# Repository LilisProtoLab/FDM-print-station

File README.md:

# FDM print station
For a number of FDM 3D printing materials it is of importance to store and use them under low relative humidity conditions. 
For this purpose a station was designed, containing an adapter drawer with two storage compartments, and three 3D printer compartments. For each compartment relative humidity (and temperature) can be monitored and controlled by flushing with dried compressed air. 

## Main features
This FDM print station contains:
+ A humidity control system
	+ Building-supplied compressed air is fed through a membrane dryer (DM08G-19KA-N) to reduce the moisture level
   	+ Each compartment contains a sensor unit which monitors temperature, humidity and door open status
   		+ Door sensors make sure flushing is only active while the compartments are closed
   	+ Five electronic valves direct the flow of pressured air to each compartment
   	+ Dried air is distributed to five compartments: two drawer compartments, and three printer compartments
   	+ Home Assistant integration controls the humidity setpoints for the drawer compartments (typically 12%) and the printer enclosures (typically 20%)
+ One filament storage drawer with two compartments
	+ A pre-existing drawer is supplemented with a transparant PMMA enclosure for convenient selection of materials with the lids closed	
	+ A screen mounted to the drawer displays the current humidity, temperature and door sensors + flushing status of all compartments
+ Three printer enclosures
	+ vertical sliding doors for minimal obstruction from 5mm PMMA sheets, with 3D printed handles and latches.
	+  The exhaust ventilation is connected to the building exhaust system and controlled via manual, 3D printed gate valves.
	+ The enclosure is made from aluminium extrusions with 3mm PMMA sheet walls

```
.
|--- Build 
|--- Docs
|--- Results
|--- Software
| LICENSE
| README.md

```

The purpose of each subfolder is explained below:
+ Build: Contains all the (binary) design files that are needed for the hardware. Use subfolder for more complex assemblies.
+ Docs: Contains the documentation of the project: background information, sources, warnings, and build instructions. 
+ Results: For measurement or functional devices, it is good to report some results as a benchmark for others who try to replicate the project.
+ Software: For hardware projects that have an operating software or firmware, it is a good versioning practice to separate the software code from build instructions.

## Build instructions
_Guide the reader with the order of browsing your project repository for an optimum building experience_
 
When you want to start a new repository, it is better that you copy this repository to your project repository and start by changing all the description.
All instructions and (sub)headers are suggestions. You can change the style, order, or composition as you see necessary. 

It would be kind if you put a shortcut to your Bill of Materials file.
This template can be copied free of charge. 

## Outcomes

## Team
+ Project initiator: Pieter Kooijman @pkooijman
+ Contributors:
	+ Josh Hauser @catoprovector
 	+ Nico van Hijningen

## Get involved
_Especially for open source projects, it is benefitial to motivate the potential users of the project to contribute back or share their feedback. Make it easy for them._

Comments and suggestions on this folder structure are always welcome. Please create an issue to share your feedback or question, or if you prefer send a pull request. 

Better structured projects can explain a number of options for contributors such as: 
+ (where to start)
+ (issue template)
+ (direct contact)
+ (pull requests)

## License
_After the README, A LICENSE is the most important file in the project documentation. Without a license, there is too much uncertainty to try building anything on top of the original project._

This project is released under CC0 1.0 Universal. 
You can modify an reuse as you like.
The project team appreciates your suggestions or examples for enhancing the repository, but your consistent documentation of your project is the best gift to the world. Hopefully, this template could make that a bit easier for you. 

### (How to cite:)
_Additionally, you can specify how other can cite your project._

## (Funding)
_Be kind to your funders and mention their support visibly and consistently. They also need to show their resources are wisely spent._

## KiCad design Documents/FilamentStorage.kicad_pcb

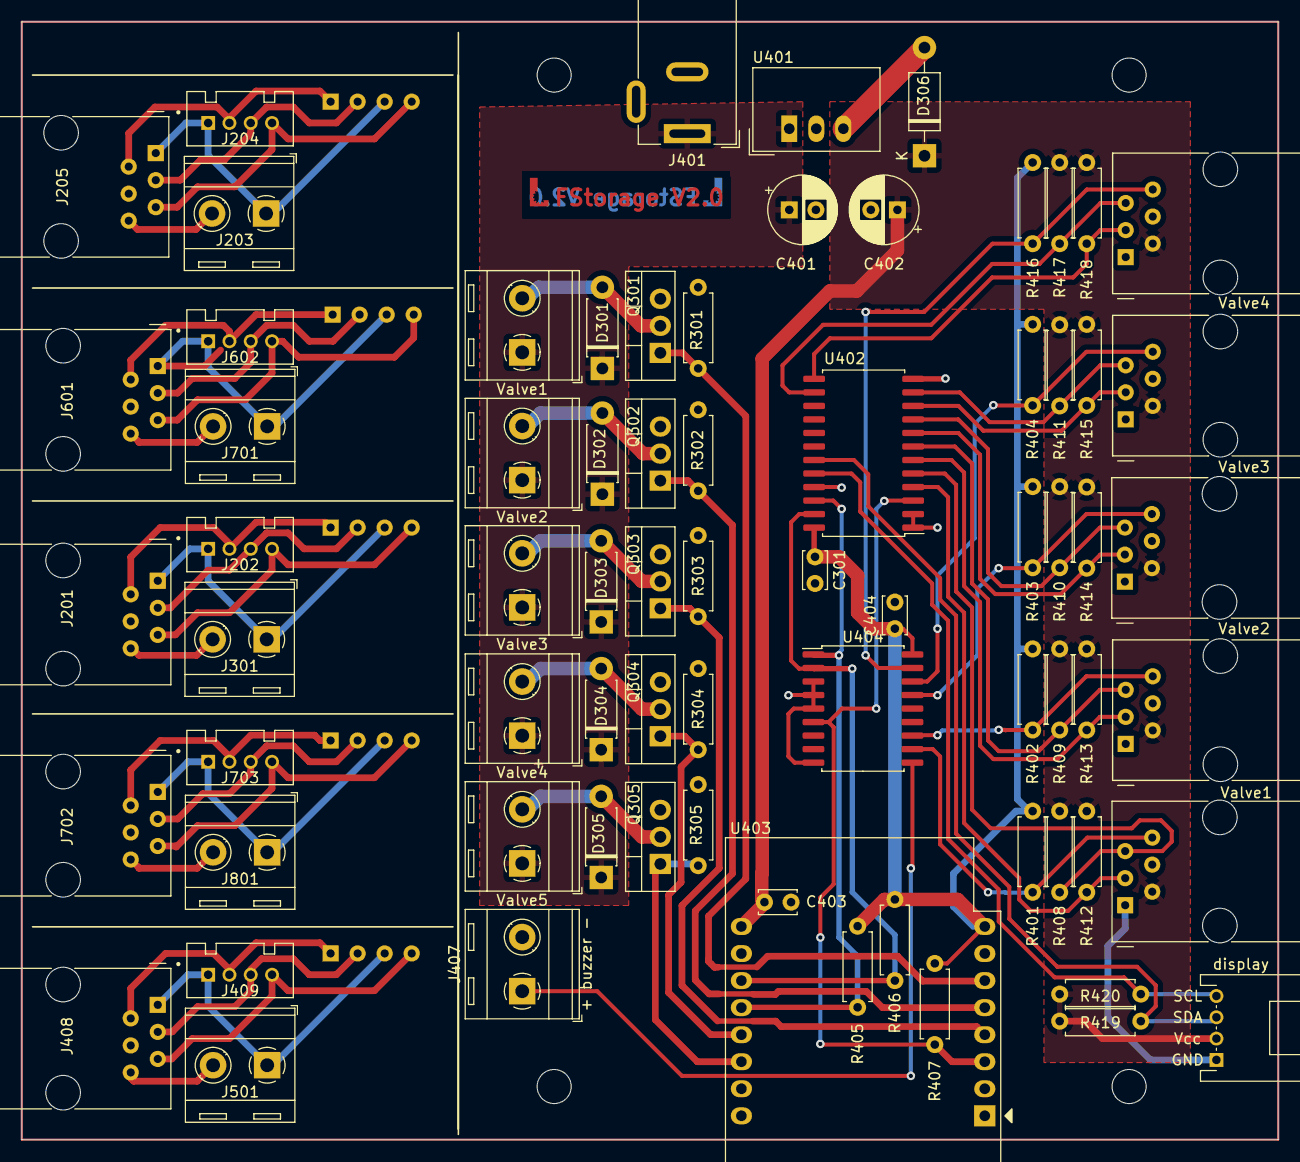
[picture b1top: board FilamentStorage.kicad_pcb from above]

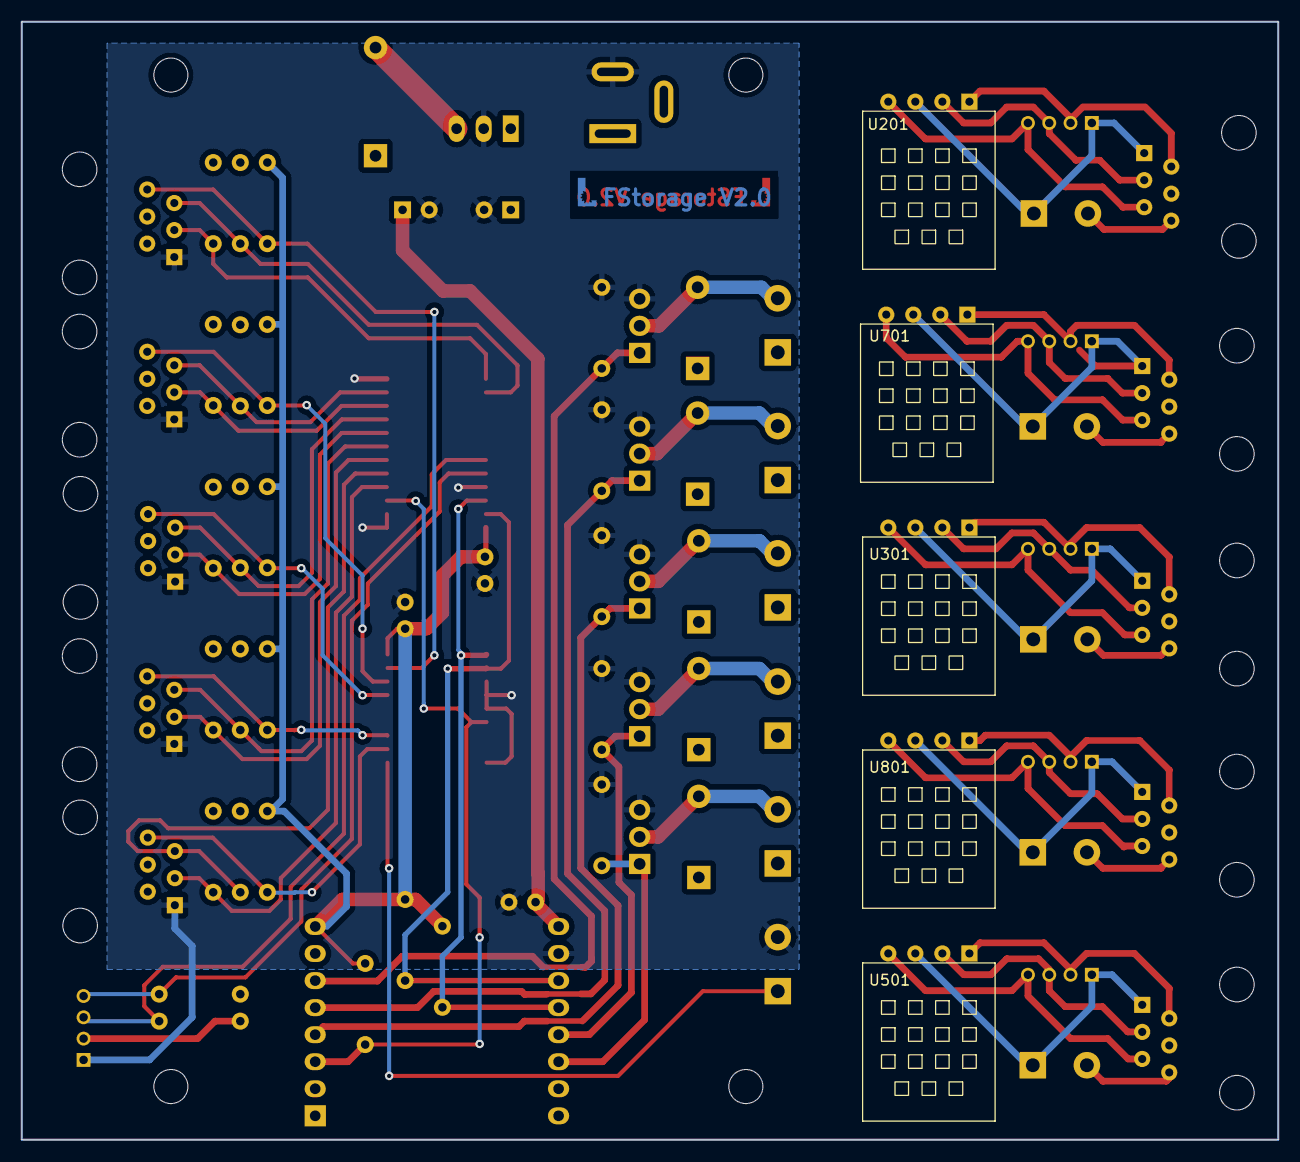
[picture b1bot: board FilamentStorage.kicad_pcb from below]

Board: 2 copper layers, 118.0 x 105.0 mm, 82 parts (5 on the bottom side), 61 nets.

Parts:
C301, C403, C404: 22n; C_Disc_D3.4mm_W2.1mm_P2.50mm
C401: 10uF/50V; CP_Radial_D6.3mm_P2.50mm
C402: 10uF/10V; CP_Radial_D6.3mm_P2.50mm
D301, D302, D303, D304, D305: 1N4007; D_DO-41_SOD81_P7.62mm_Horizontal
D306: 1N5817; D_DO-41_SOD81_P10.16mm_Horizontal
H301, H302, H303, H304: MountingHole; MountingHole_3.2mm_M3
J201, J205, J408, J601, J702: 6P6C; RJ12_Amphenol_54601
J202, J204, J409, J602, J703: I2C; grove_4p_vert
J203, J301, J501, J701, J801: Screw_Terminal_01x02; TerminalBlock_RND_205-00287_1x02_P5.08mm_Horizontal
J303: Valve1; TerminalBlock_RND_205-00287_1x02_P5.08mm_Horizontal
J304: Valve2; TerminalBlock_RND_205-00287_1x02_P5.08mm_Horizontal
J305: Valve3; TerminalBlock_RND_205-00287_1x02_P5.08mm_Horizontal
J306: Valve4; TerminalBlock_RND_205-00287_1x02_P5.08mm_Horizontal
J307: Valve5; TerminalBlock_RND_205-00287_1x02_P5.08mm_Horizontal
J401: Barrel_Jack_Switch; BarrelJack_Wuerth_6941xx301002
J402: display; grove_4p_hor
J403: Valve1; RJ12_Amphenol_54601
J404: Valve2; RJ12_Amphenol_54601
J405: Valve3; RJ12_Amphenol_54601
J406: Valve4; RJ12_Amphenol_54601
J407: + buzzer -; TerminalBlock_RND_205-00287_1x02_P5.08mm_Horizontal
J410: Valve5; RJ12_Amphenol_54601
Q301, Q302, Q303, Q304, Q305: IRLZ34N; TO-220-3_Vertical
R301, R302, R303, R304, R305, R405, R406, R408, R409, R410, R411, R412, R413, R414, R415, R417, R418, R419, R420: 4k7; R_Axial_DIN0207_L6.3mm_D2.5mm_P7.62mm_Horizontal
R401, R402, R403, R404, R407, R416: 10k; R_Axial_DIN0207_L6.3mm_D2.5mm_P7.62mm_Horizontal
U201, U301, U501, U701, U801: AM2320; AM2320_horizontal
U401: TSR_1-2450; Converter_DCDC_TRACO_TSR-1_THT
U402: PCA9548ADW; SOIC-24W_7.5x15.4mm_P1.27mm
U403: WeMos_D1_mini V3; WEMOS_D1_mini_light
U404: MCP23008-xSO; SOIC-18W_7.5x11.6mm_P1.27mm

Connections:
+3V3: C301.1, C404.1, R401.2, R402.2, R403.2, R404.2, R405.2, R406.2, R407.2, R416.2, U402.24 (VCC), U403.8 (3V3), U404.18 (VDD)
+5V: C402.1, C403.1, D306.1 (K), J402.2, J403.2, J404.2, J405.2, J406.2, J410.2, R408.1, R409.1, R410.1, R411.1, R412.1, R413.1, R414.1, R415.1, R417.1, R418.1, R419.2, R420.2, U403.9 (5V)
/12VA: C401.1, D301.1 (K), D302.1 (K), D303.1 (K), D304.1 (K), D305.1 (K), J303.1, J304.1, J305.1, J306.1, J307.1, J401.1, U401.1 (Vin)
/Cabinet1/shield: J408.1, J409.1, J501.1, U501.3 (gnd)
/Cabinet2/shield: J601.1, J602.1, J701.1, U701.3 (gnd)
/Cabinet3/shield: J702.1, J703.1, J801.1, U801.3 (gnd)
/Cabinet4/shield: J203.1, J204.1, J205.1, U201.3 (gnd)
/Cabinet/shield: J201.1, J202.1, J301.1, U301.3 (gnd)
/Main board/b1: J407.1, U404.10 (GP0)
/Main board/s1: J403.6, R401.1, U404.11 (GP1)
/Main board/s2: J404.6, R402.1, U404.12 (GP2)
/Main board/s3: J405.6, R403.1, U404.15 (GP5)
/Main board/s4: J406.6, R404.1, U404.16 (GP6)
/Main board/s5: J410.6, R416.1, U404.17 (GP7)
/Main board/v1: Q301.1 (G), R301.1, U403.6 (MOSI/D7)
/Main board/v2: Q302.1 (G), R302.1, U403.5 (MISO/D6)
/Main board/v3: Q303.1 (G), R303.1, U403.4 (SCK/D5)
/Main board/v4: Q304.1 (G), R304.1, U403.13 (SDA/D2)
/Main board/v5: Q305.1 (G), R305.1, U403.14 (SCL/D1)
GND: C301.2, C401.2, C402.2, C403.2, C404.2, J401.2, J402.1, J403.1, J404.1, J405.1, J406.1, J407.2, J410.1, Q301.3 (S), Q302.3 (S), Q303.3 (S), Q304.3 (S), Q305.3 (S), R301.2, R302.2, R303.2, R304.2, R305.2, U401.2 (GND), U402.1 (A0), U402.2 (A1), U402.12 (GND), U402.21 (A2), U403.10 (GND), U404.3 (A2), U404.4 (A1), U404.5 (A0), U404.9 (VSS)
unnamed: D301.2 (A), J303.2, Q301.2 (D)
unnamed: D302.2 (A), J304.2, Q302.2 (D)
unnamed: D303.2 (A), J305.2, Q303.2 (D)
unnamed: D304.2 (A), J306.2, Q304.2 (D)
unnamed: D305.2 (A), J307.2, Q305.2 (D)
unnamed: D306.2 (A), U401.3 (Vout)
unnamed: J201.2, J202.2, U301.1 (Vcc)
unnamed: J201.3, J202.3, U301.2 (SDA)
unnamed: J201.5, J202.4, U301.4 (SCL)
unnamed: J201.6, J301.2
unnamed: J203.2, J205.6
unnamed: J204.2, J205.2, U201.1 (Vcc)
unnamed: J204.3, J205.3, U201.2 (SDA)
unnamed: J204.4, J205.5, U201.4 (SCL)
unnamed: J402.3, R419.1, U402.19 (SD7)
unnamed: J402.4, R420.1, U402.20 (SC7)
unnamed: J403.3, R412.2, U402.4 (SD0)
unnamed: J403.5, R408.2, U402.5 (SC0)
unnamed: J404.3, R413.2, U402.6 (SD1)
unnamed: J404.5, R409.2, U402.7 (SC1)
unnamed: J405.3, R414.2, U402.8 (SD2)
unnamed: J405.5, R410.2, U402.9 (SC2)
unnamed: J406.3, R415.2, U402.10 (SD3)
unnamed: J406.5, R411.2, U402.11 (SC3)
unnamed: J408.2, J409.2, U501.1 (Vcc)
unnamed: J408.3, J409.3, U501.2 (SDA)
unnamed: J408.5, J409.4, U501.4 (SCL)
unnamed: J408.6, J501.2
unnamed: J410.3, R418.2, U402.13 (SD4)
unnamed: J410.5, R417.2, U402.14 (SC4)
unnamed: J601.2, J602.2, U701.1 (Vcc)
unnamed: J601.3, J602.3, U701.2 (SDA)
unnamed: J601.5, J602.4, U701.4 (SCL)
unnamed: J601.6, J701.2
unnamed: J702.2, J703.2, U801.1 (Vcc)
unnamed: J702.3, J703.3, U801.2 (SDA)
unnamed: J702.5, J703.4, U801.4 (SCL)
unnamed: J702.6, J801.2
unnamed: R405.1, U402.22 (SCL), U403.12 (D3), U404.1 (SCL)
unnamed: R406.1, U402.23 (SDA), U403.11 (D4), U404.2 (SDA)
unnamed: R407.1, U402.3 (~RESET), U403.3 (D0), U404.6 (~RESET)

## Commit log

2024-12-17 renamed file structure
2024-12-17 add instructions
2024-12-17 check
2024-12-17 added code
2025-01-07 Update LICENSE
2025-01-07 added photo
2025-06-06 added ESP code
2025-06-06 added PCB design files
